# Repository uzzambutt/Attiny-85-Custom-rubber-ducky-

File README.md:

# Attiny-85-Custom-rubber-ducky

> Made by uzzam for HackClub Blueprint.
> Its a custom rubber ducky that runs the same scripts as the original rubber ducky.

## Features
1: Runs on an Atmel Tiny 85 MCU
2: very smol size

## Images

***schematic***

***3D Front***

## BOM.csv

| Reference | Qty | Value            | Cost (USD) | Footprint                      | Source                                                              |
| --------- | --- | ---------------- | ---------- | ------------------------------ | ------------------------------------------------------------------- |
| D1        | 1   | 1N5819           | 1.00       | Diode_SMD:D_0603_1608Metric    | [AliExpress](https://www.aliexpress.com/item/1005005817497813.html) |
| D2, D3    | 2   | BZV55B3V6        | 3.00       | Diode_SMD:D_MiniMELF           | [AliExpress](https://www.aliexpress.com/item/1005003276154390.html) |
| D4        | 1   | Yellow LED       | 2.00       | LED_SMD:LED_0805_2012Metric    | [AliExpress](https://www.aliexpress.com/item/32885825492.html)      |
| PWR1      | 1   | Purple LED       | 3.00       | LED_SMD:LED_0805_2012Metric    | [AliExpress](https://www.aliexpress.com/item/32885825492.html)      |
| J1        | 1   | Conn 1×03 Socket | —          | PinHeader_1x03_P2.54mm         | —                                                                   |
| J2        | 1   | Conn 1×06 Socket | —          | PinHeader_1x06_P2.54mm         | —                                                                   |
| J3        | 1   | USB-A Connector  | —          | USB PCB Connector              | —                                                                   |
| R1        | 1   | 1.5 kΩ           | 3.00       | Resistor_SMD:R_0603_1608Metric | [AliExpress](https://www.aliexpress.com/item/1005002991861666.html) |
| R2, R3    | 2   | 68 Ω             | 3.00       | Resistor_SMD:R_0603_1608Metric | [AliExpress](https://www.aliexpress.com/item/1005002991861666.html) |
| R4, R5    | 2   | 1 kΩ             | 3.00       | Resistor_SMD:R_0603_1608Metric | [AliExpress](https://www.aliexpress.com/item/1005002991861666.html) |
| U1        | 1   | MC7805           | 2.50       | TO-252-2                       | [AliExpress](https://www.aliexpress.com/item/1005009481715148.html) |
| U2        | 1   | ATtiny85-20PU    | 10.00      | SOIC-8                         | [AliExpress](https://www.aliexpress.com/item/1005007199030119.html) |

> Prices are approximate in this BOM without Taxes and shipping fees.

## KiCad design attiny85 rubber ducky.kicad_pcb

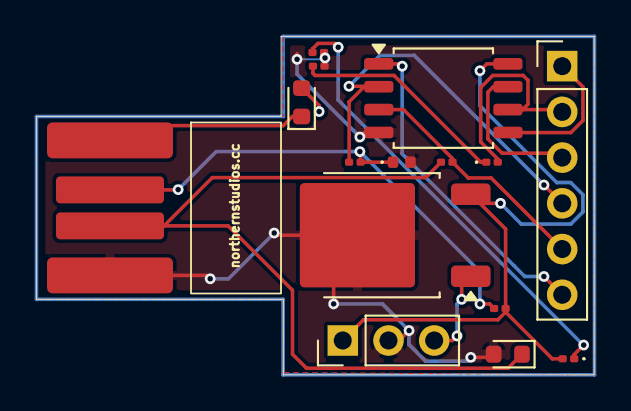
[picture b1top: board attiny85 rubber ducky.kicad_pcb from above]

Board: 4 copper layers, 31.0 x 18.8 mm, 15 parts (0 on the bottom side), 14 nets.

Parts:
D1: D; D_0603_1608Metric
D2: BZV55B3V6; D_0603_1608Metric
D3: BZV55B3V6; D_0402_1005Metric
D4: LED; LED_0201_0603Metric
J1: Conn_01x03_Socket; PinHeader_1x03_P2.54mm_Vertical
J2: Conn_01x06_Socket; PinHeader_1x06_P2.54mm_Vertical
J3: USB_A; USB_PCB_connector
PWR1: LED; LED_0201_0603Metric
R1: 1500; R_0201_0603Metric
R2, R3: 66.5; R_0201_0603Metric
R4, R5: 1K; R_0201_0603Metric
U1: MC78M05_TO252; TO-252-2
U2: ATtiny85-20S; SOIC-8_5.3x5.3mm_P1.27mm

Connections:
+5V: D1.2 (A), J1.1, PWR1.2 (A), R1.2, U1.3 (VO), U2.8 (VCC)
GND: D2.2 (A), D3.2 (A), J1.2, J3.4 (GND), R4.2, R5.2, U1.2 (GND), U2.4 (GND)
unnamed: D1.1 (K), J3.1 (VBUS)
unnamed: D2.1 (K), J3.3 (D+), R3.1
unnamed: D3.1 (K), J3.2 (D-), R1.1, R2.1
unnamed: D4.2 (A), J2.2, U2.6 (PB1)
unnamed: D4.1 (K), R5.1
unnamed: J1.3, U1.1 (VI)
unnamed: J2.1, U2.5 (AREF/PB0)
unnamed: J2.3, U2.7 (PB2)
unnamed: J2.4, R2.2, U2.2 (XTAL1/PB3)
unnamed: J2.5, R3.2, U2.3 (XTAL2/PB4)
unnamed: J2.6, U2.1 (~RESET/PB5)
unnamed: PWR1.1 (K), R4.1

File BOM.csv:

"Reference","Qty","Value","DNP","Exclude from BOM","Exclude from Board","Footprint","Datasheet"
"D1","1","D","","","","Diode_SMD:D_0603_1608Metric","~"
"D2,D3","2","BZV55B3V6","","","","Diode_SMD:D_MiniMELF","https://assets.nexperia.com/documents/data-sheet/BZV55_SER.pdf"
"D4,PWR1","2","LED","","","","LED_SMD:LED_0805_2012Metric","~"
"J1","1","Conn_01x03_Socket","","","","Connector_PinHeader_2.54mm:PinHeader_1x03_P2.54mm_Vertical","~"
"J2","1","Conn_01x06_Socket","","","","Connector_PinHeader_2.54mm:PinHeader_1x06_P2.54mm_Vertical","~"
"J3","1","USB_A","","","","USBA FOOTPRINT PCB:USB_PCB_connector","~"
"R1","1","1500","","","","Resistor_SMD:R_0603_1608Metric","~"
"R2,R3","2","66.5","","","","Resistor_SMD:R_0603_1608Metric","~"
"R4,R5","2","1K","","","","Resistor_SMD:R_0603_1608Metric","~"
"U1","1","MC78M05_TO252","","","","Package_TO_SOT_SMD:TO-252-2","https://www.onsemi.com/pub/Collateral/MC78M00-D.PDF"
"U2","1","ATtiny85-20S","","","","Package_SO:SOIC-8_5.3x5.3mm_P1.27mm","http://ww1.microchip.com/downloads/en/DeviceDoc/atmel-2586-a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"

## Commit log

2025-12-04 Create E
2025-12-04 Update README with additional images
    Added new images to the README file.
